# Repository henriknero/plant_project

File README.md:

# plant_project

## Flashing EEPROM with INIT Values
### Linux
```
/home/john/.arduino15/packages/arduino/tools/avrdude/6.3.0-arduino17/bin/avrdude -C/home/john/.arduino15/packages/arduino/tools/avrdude/6.3.0-arduino17/etc/avrdude.conf -pattiny85 -cstk500v1 -P/dev/ttyACM0 -b19200 -u -U eeprom:w:eeprom.hex:i
```
### Windows
```
C:\Users\henner\AppData\Local\Arduino15\packages\arduino\tools\avrdude\6.3.0-arduino17/bin/avrdude -CC:\Users\henner\AppData\Local\Arduino15\packages\arduino\tools\avrdude\6.3.0-arduino17/etc/avrdude.conf -pattiny85 -cstk500v1 -PCOM6 -b19200 -u -U eeprom:w:eeprom.hex:i
```
## Fetching logs from EEPROM
The values will be in same format as eeprom.hex file. Each byte except for the first 2bytes will represent a 0-255 value of how moist the soil is. 
### Linux
```
/home/john/.arduino15/packages/arduino/tools/avrdude/6.3.0-arduino17/bin/avrdude -C/home/john/.arduino15/packages/arduino/tools/avrdude/6.3.0-arduino17/etc/avrdude.conf -pattiny85 -cstk500v1 -P/dev/ttyACM0 -b19200 -u -U eeprom:r:result.hex:i
```
### Windows
```
C:\Users\henner\AppData\Local\Arduino15\packages\arduino\tools\avrdude\6.3.0-arduino17/bin/avrdude -CC:\Users\henner\AppData\Local\Arduino15\packages\arduino\tools\avrdude\6.3.0-arduino17/etc/avrdude.conf -pattiny85 -cstk500v1 -PCOM6 -b19200 -u -U eeprom:r:result.hex:i
```

## Future improvements
* Setting watering trigger value from EEPROM to be able to easily program the unit for different moisture levels.
* Setting watering trigger value using button (Not sure I want this.)

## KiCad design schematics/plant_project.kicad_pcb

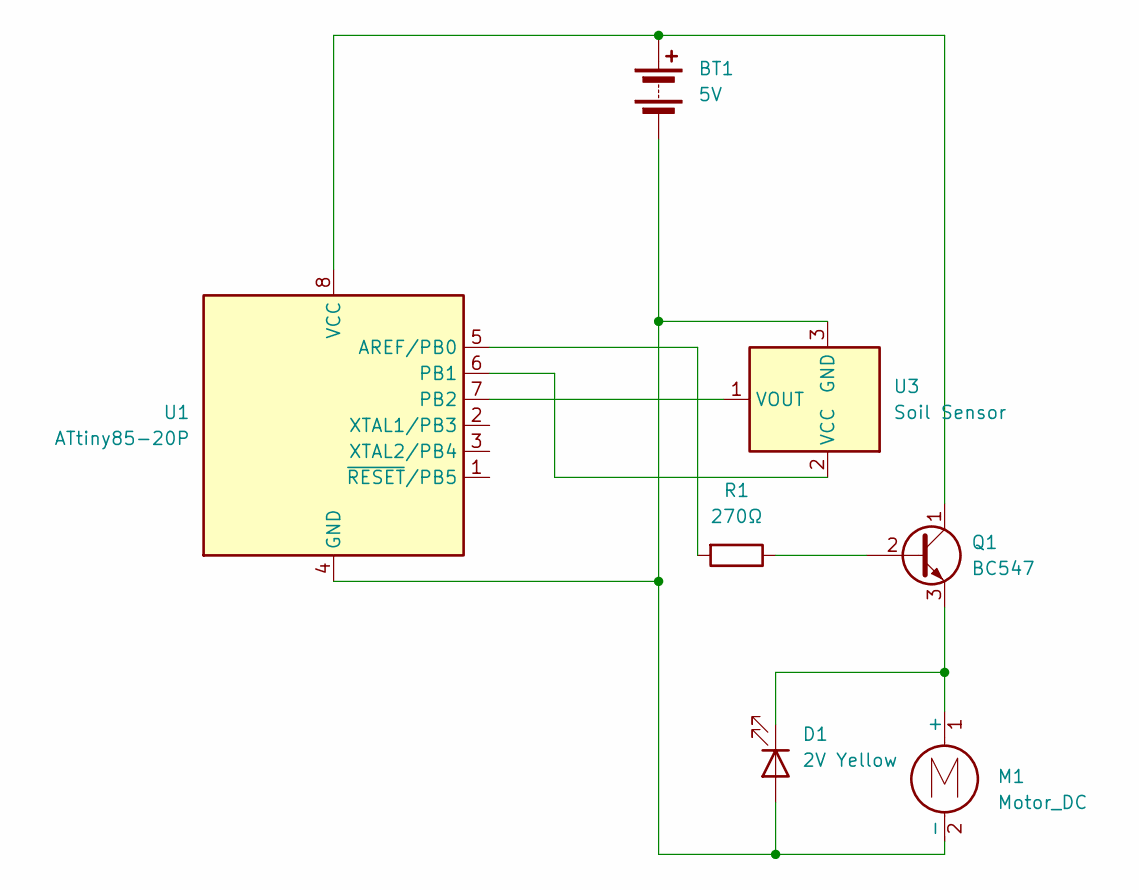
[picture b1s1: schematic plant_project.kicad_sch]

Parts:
BT1: 5V; PinHeader_1x02_P2.54mm_Vertical
D1: 2V Yellow; LED_D5.0mm
M1: Motor_DC; PinHeader_1x02_P2.54mm_Vertical
Q1: BC547; TO-92_Inline
R1: 270Ω; R_Axial_DIN0414_L11.9mm_D4.5mm_P15.24mm_Horizontal
U1: ATtiny85-20P; DIP-8_W7.62mm
U3: Soil Sensor; PinHeader_1x03_P2.54mm_Vertical

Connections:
unnamed: BT1.1 (+), Q1.1 (C), U1.8 (VCC)
unnamed: BT1.2 (-), D1.2 (A), M1.2 (-), U1.4 (GND), U3.3 (GND)
unnamed: D1.1 (K), M1.1 (+), Q1.3 (E)
unnamed: Q1.2 (B), R1.1
unnamed: R1.2, U1.5 (AREF/PB0)
unnamed: U1.6 (PB1), U3.2 (VCC)
unnamed: U1.7 (PB2), U3.1 (VOUT)

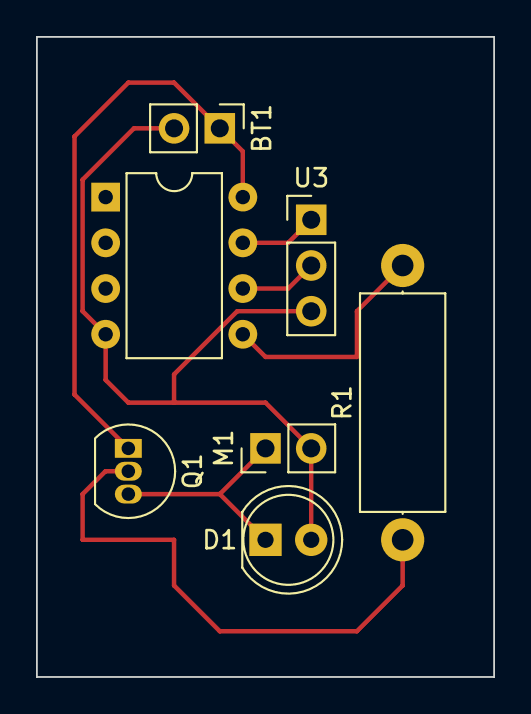
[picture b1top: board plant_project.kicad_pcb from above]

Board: 2 copper layers, 25.4 x 35.6 mm, 7 parts (0 on the bottom side), 7 nets.

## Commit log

2024-01-15 Putting it all together and add snore lib for deep sleep
2024-01-20 Update code to work with EEPROM
2024-01-20 Final modifications for logging
2024-01-29 Added Moisture Sensitivity to EEPROM
